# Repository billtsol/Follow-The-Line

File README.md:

# Arduino Follow-the-Line Project with QTR Reflectance Sensor

This project is an example of how to use an Arduino board, QTR reflectance sensor, and a motor driver shield to create a simple follow-the-line robot.

## Requirements

To build this project, you will need the following components:

- Arduino board
- QTR reflectance sensor
- Motor driver shield
- Wheels
- Motors
- Jumper wires
- Battery

## Circuit Diagram

## PCB

## Code

The code for this project is available in the `follow_the_line.ino` file.
You can also open the `qtr_xA_example.ino` file that includes an example of how to use the QTR reflectance sensor as an analog sensor to detect the position of a line.

## Installation

1. Download the Arduino IDE from the official website and install it on your computer.
2. Connect your Arduino board to your computer via USB cable.
3. Open the Arduino IDE and open the `follow_the_line.ino` file.
4. Upload the code to your Arduino board by clicking the "Upload" button in the IDE.

## Usage

1. Connect the QTR reflectance sensor and the motor driver shield to your Arduino board according to the circuit diagram.
2. Attach the wheels and motors to the chassis.
3. Connect the motors to the motor driver shield.
4. Connect the battery to the motor driver shield.
5. Turn on the power and place the robot on a black line on a white background.
6. The robot will follow the line until it reaches the end of the line.

## Troubleshooting

If the robot does not follow the line correctly, you may need to adjust the threshold values in the code or adjust the position of the QTR reflectance sensor.

## Feature thoughts for this project:

1. Add some LEDs to make the car follow the line in the dark: By adding some LEDs to the front of the robot, it can detect the line even in low light conditions. The LEDs can be programmed to turn on when the QTR sensor detects the line and turn off when it doesn't. This feature can improve the robot's performance in darker environments.

2. Add some obstacle sensors to avoid objects in line: By adding some obstacle sensors to the sides of the robot, it can detect if there are any obstacles in its path and avoid them while staying on the line. This feature can improve the safety of the robot and prevent it from crashing into objects while following the line.

## Final Images

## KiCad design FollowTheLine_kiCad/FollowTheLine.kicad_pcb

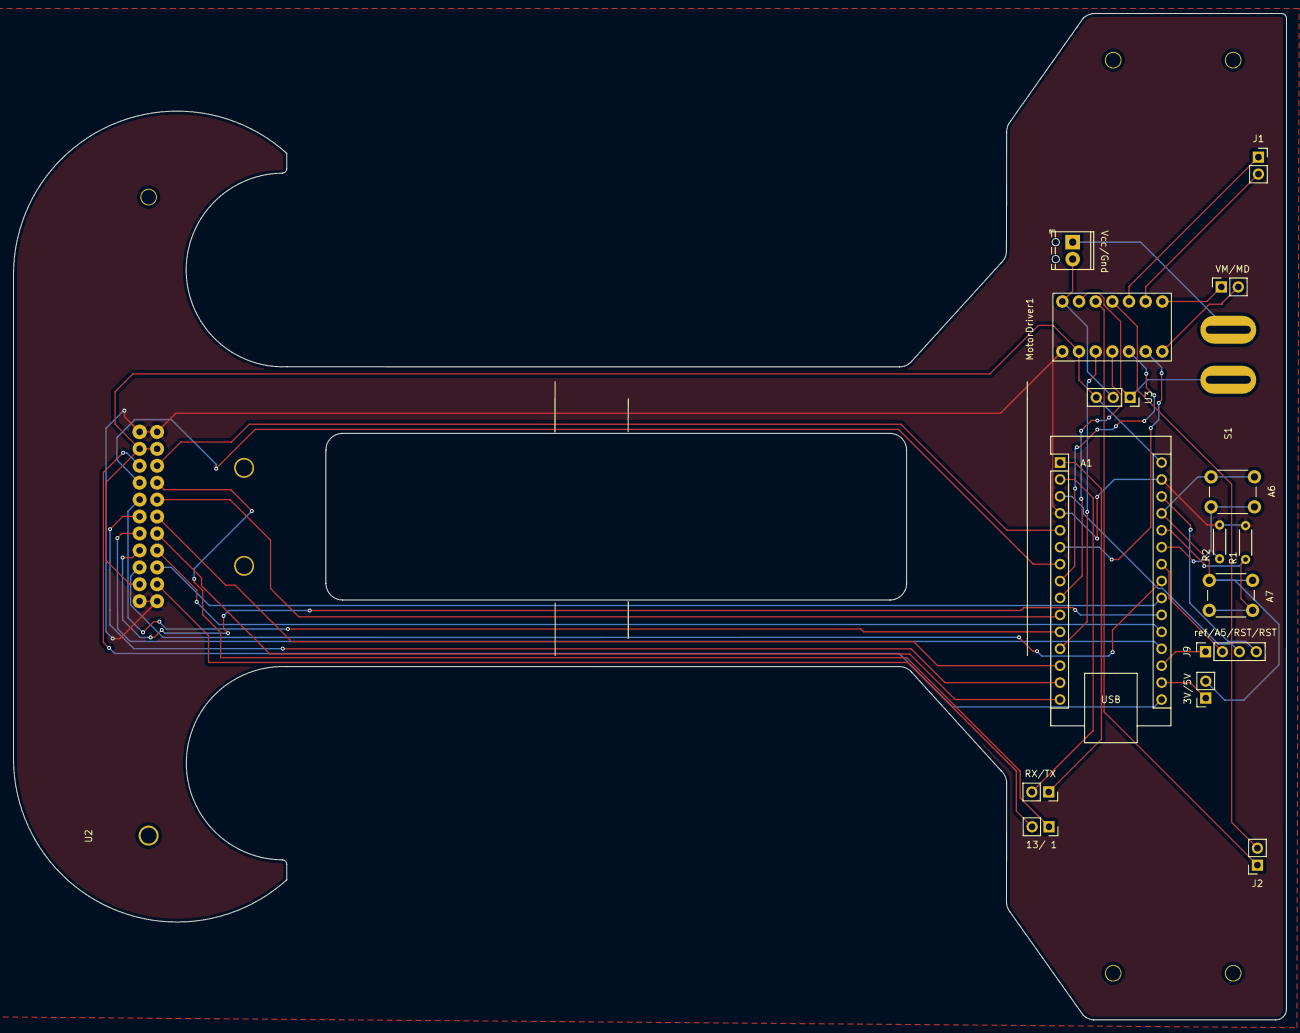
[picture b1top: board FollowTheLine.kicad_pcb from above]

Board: 2 copper layers, 191.0 x 151.0 mm, 17 parts (0 on the bottom side), 40 nets.

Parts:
A1: Arduino_Nano_Every; Arduino_Nano
A6, A7: SW_Push; SW_PUSH_6mm
J1, J2, J3, J5, J6, J18: Socket_02; PinSocket_1x02_P2.54mm_Vertical
J4: Screw_Terminal; TerminalBlock_Phoenix_MPT-0,5-2-2.54_1x02_P2.54mm_Horizontal
J9: Socket_04; PinSocket_1x04_P2.54mm_Vertical
MotorDriver1: DRV8835
R1, R2: 1kΩ; R_Axial_DIN0204_L3.6mm_D1.6mm_P5.08mm_Horizontal
S1: RB141C1100; SW_RB141C1100
U2: Array Reflectance Sensor; QTRX-13RC
U3: L7805; PinSocket_1x03_P2.54mm_Vertical

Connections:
+12V: MotorDriver1.VCC_HightVolt, S1.2, U3.1 (IN)
/3V3_out: A1.17 (3V3), J6.1
/A5: A1.24 (SCL/A5), J9.2
/A6: A1.25 (A6), A6.2, R2.1
/A7: A1.26 (A7), A7.2, R1.1
/HighVolt_out: A1.27 (+5V), A6.1, A7.1, J6.2
/Led3: A1.10 (D7), U2.LED3
/Led4: A1.11 (D8), U2.LED4
/Led5: A1.13 (D10), U2.LED5
/Led8: A1.19 (A0), U2.LED8
/Led9: A1.20 (A1), U2.LED9
/Led11: A1.22 (A3), U2.LED11
/Led12: A1.23 (SDA/A4), U2.LED12
/MotorAenb: A1.8 (D5), MotorDriver1.AENBL
/MotorAinput: A1.6 (D3), MotorDriver1.APHASE
/MotorBenb: A1.12 (D9), MotorDriver1.BENBL
/MotorBinput: A1.9 (D6), MotorDriver1.BPHASE
/ODD: A1.5 (D2), U2.ODD
/QTRX_pin1_out: J18.1, U2.LED1
/QTRX_pin13_out: J18.2, U2.LED13
/RESET1: A1.3 (~RESET), J9.3
/RESET2: A1.28 (~RESET), J9.4
/led2: A1.7 (D4), U2.LED2
/led10: A1.21 (A2), U2.LED10
/pin1_qtrx_in (TX): A1.1 (TX1), J5.1
/pin11_led6: A1.14 (MOSI), U2.LED6
/pin12_led7: A1.15 (MISO), U2.LED7
/pin13_EVEN: A1.16 (SCK), U2.EVEN
/pin13_qtrx_in (RX): A1.2 (RX1), J5.2
/ref: A1.18 (AREF), J9.1
GND: A1.4 (GND), A1.29 (GND), MotorDriver1.GND, R1.2, R2.2, U2.GND
GND2: J4.2, MotorDriver1.GND_HigtVolt, U3.2 (GND)
unnamed: J1.1, MotorDriver1.Aout2
unnamed: J1.2, MotorDriver1.Aout1
unnamed: J2.1, MotorDriver1.Bout2
unnamed: J2.2, MotorDriver1.Bout1
unnamed: J3.1, MotorDriver1.VMM
unnamed: J3.2, MotorDriver1.MODE
unnamed: J4.1, S1.1
VCC: A1.30 (VIN), MotorDriver1.VCC, U2.VCC, U3.3 (OUT)

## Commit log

2023-04-12 Add readme.md file
2023-04-12 i add the example info for qtr sensor
2023-04-12 change some text in readme.md and add the qtr example file
2023-04-12 add follow the line arduino file
2023-04-12 add Feature thoughts in readme.md
2023-04-12 remove unused files
2024-01-23 qtr sensor code
2024-01-25 Control motors
2024-03-06 motor driver test code
2024-03-06 QTR-RC sensor test code
2024-03-06 Follow the line Initial file
2024-03-06 Remove unused folders
2024-03-10 Change some connections and start the main PID system
2024-03-11 Kicad schematic first idea - Custom qtr and motor driver footprint (what have issues)
2024-03-12 First version of follow the line pcb - only schematic
2024-03-13 version 1 follow the line
2024-03-15 Follow the line. PCB version v2
2024-03-16 kicad footprint version 2
2024-03-17 pcb completed
2024-03-17 First order. 'gerber files'
2024-03-21 new follow the line Main code. 'perfect' line tracking. And rename qtr and main folder
2024-03-22 Follow the line, pcb, Kicad Last version. (production).
2024-03-23 more accurate Kp,Ki,Kd values
2024-03-23 second version of code
2024-03-24 Make test functions, and complete the start and callibration buttons.
2024-03-25 Small changes in kiCad PCB
2024-03-29 follow the line robot with qtrx sensor
2024-03-29 Small Changes in kiCad files
2024-03-30 Version 6 in Heron project
2024-03-31 Version 2 in adv follow the line
2024-04-02 Version 3 - Add Start and End point recognition function.
2024-04-05 More accurate hp,ki,pd. not working
2024-04-08 PID controller completed. base speed 100 max speed 200.
2024-05-05 Add the circuit diagram (pdf)
2024-06-03 kicad backups
2024-06-11 remove backups
2024-06-12 pcb image
2024-07-07 implement circuit and pcb diagrams
2024-07-08 Add final images
2024-07-11 robot image without background
